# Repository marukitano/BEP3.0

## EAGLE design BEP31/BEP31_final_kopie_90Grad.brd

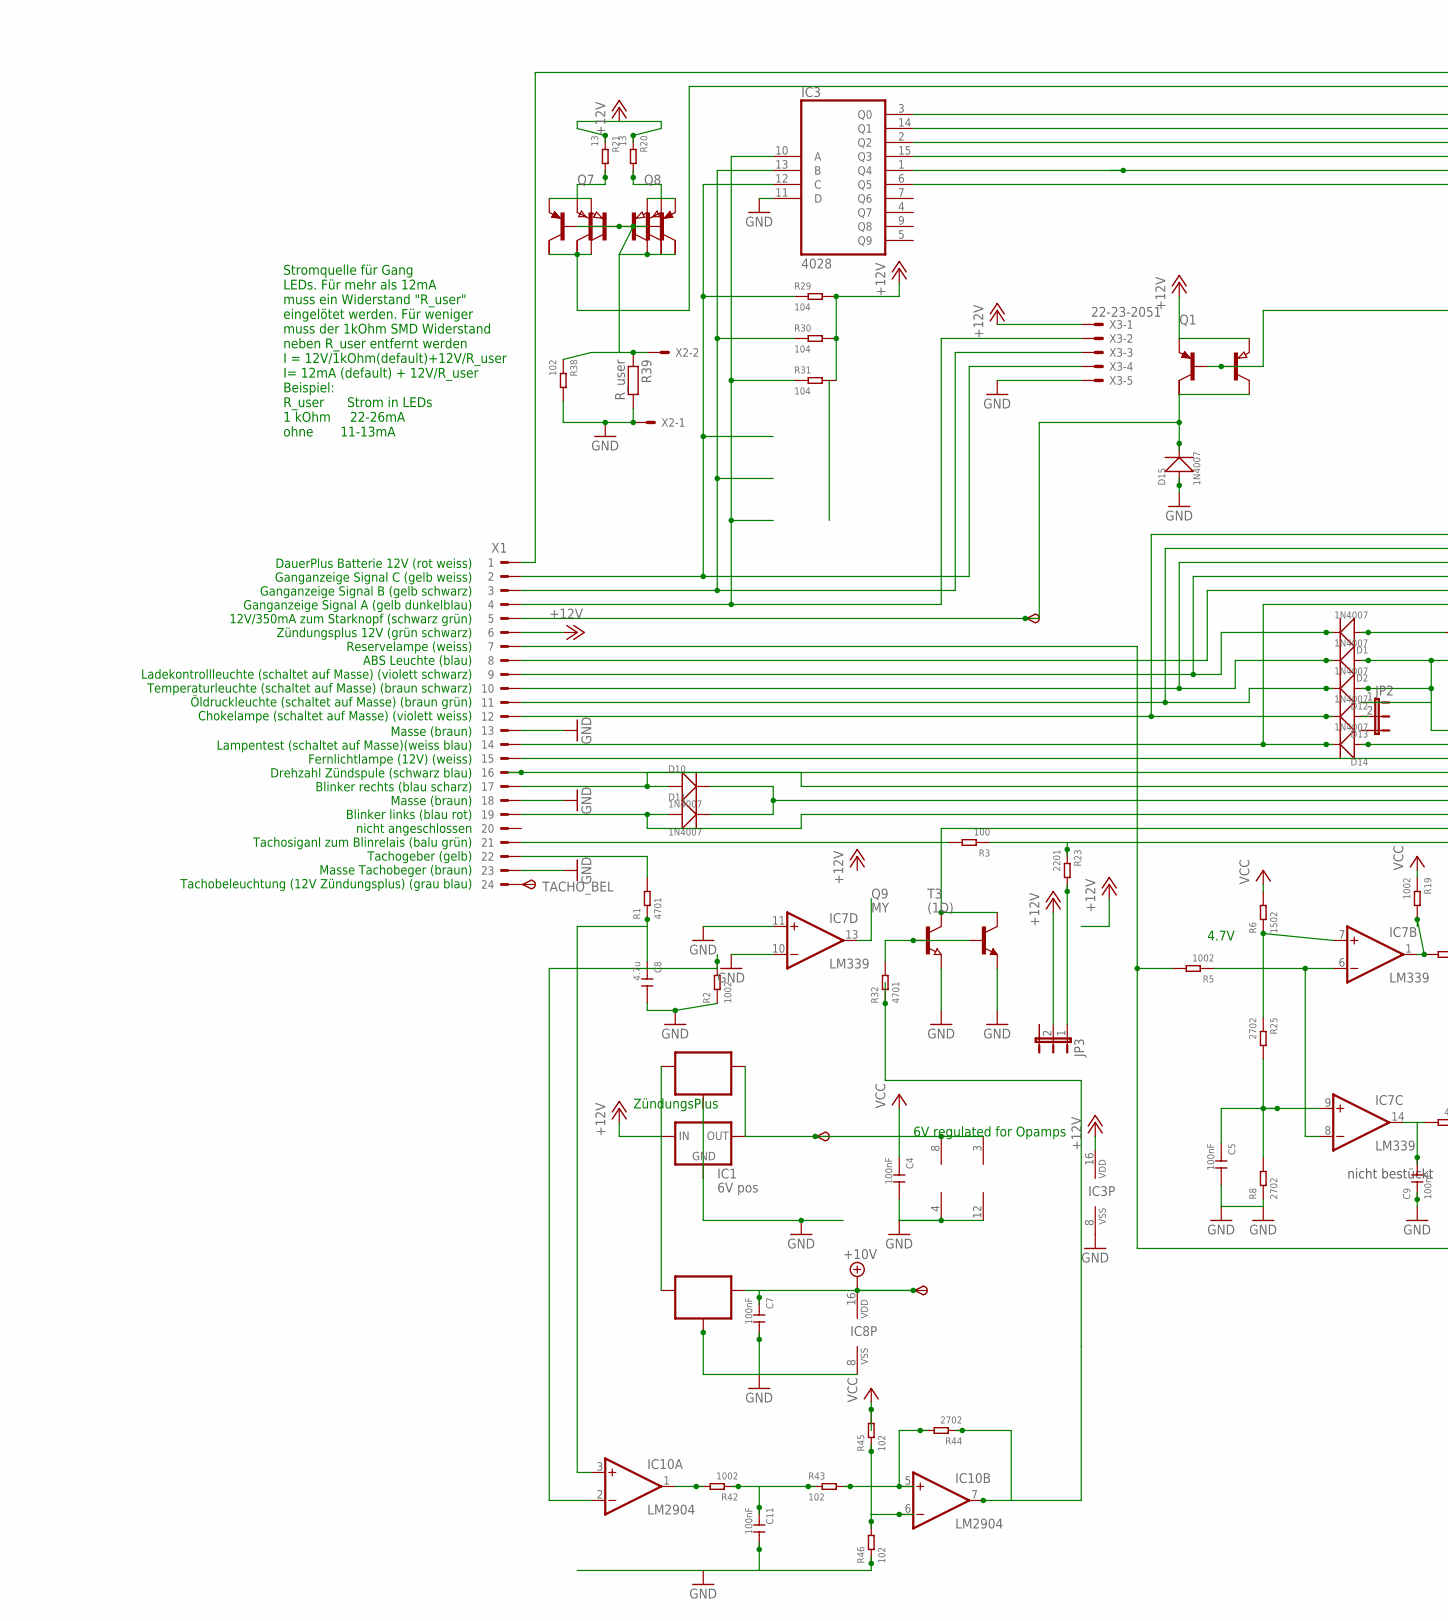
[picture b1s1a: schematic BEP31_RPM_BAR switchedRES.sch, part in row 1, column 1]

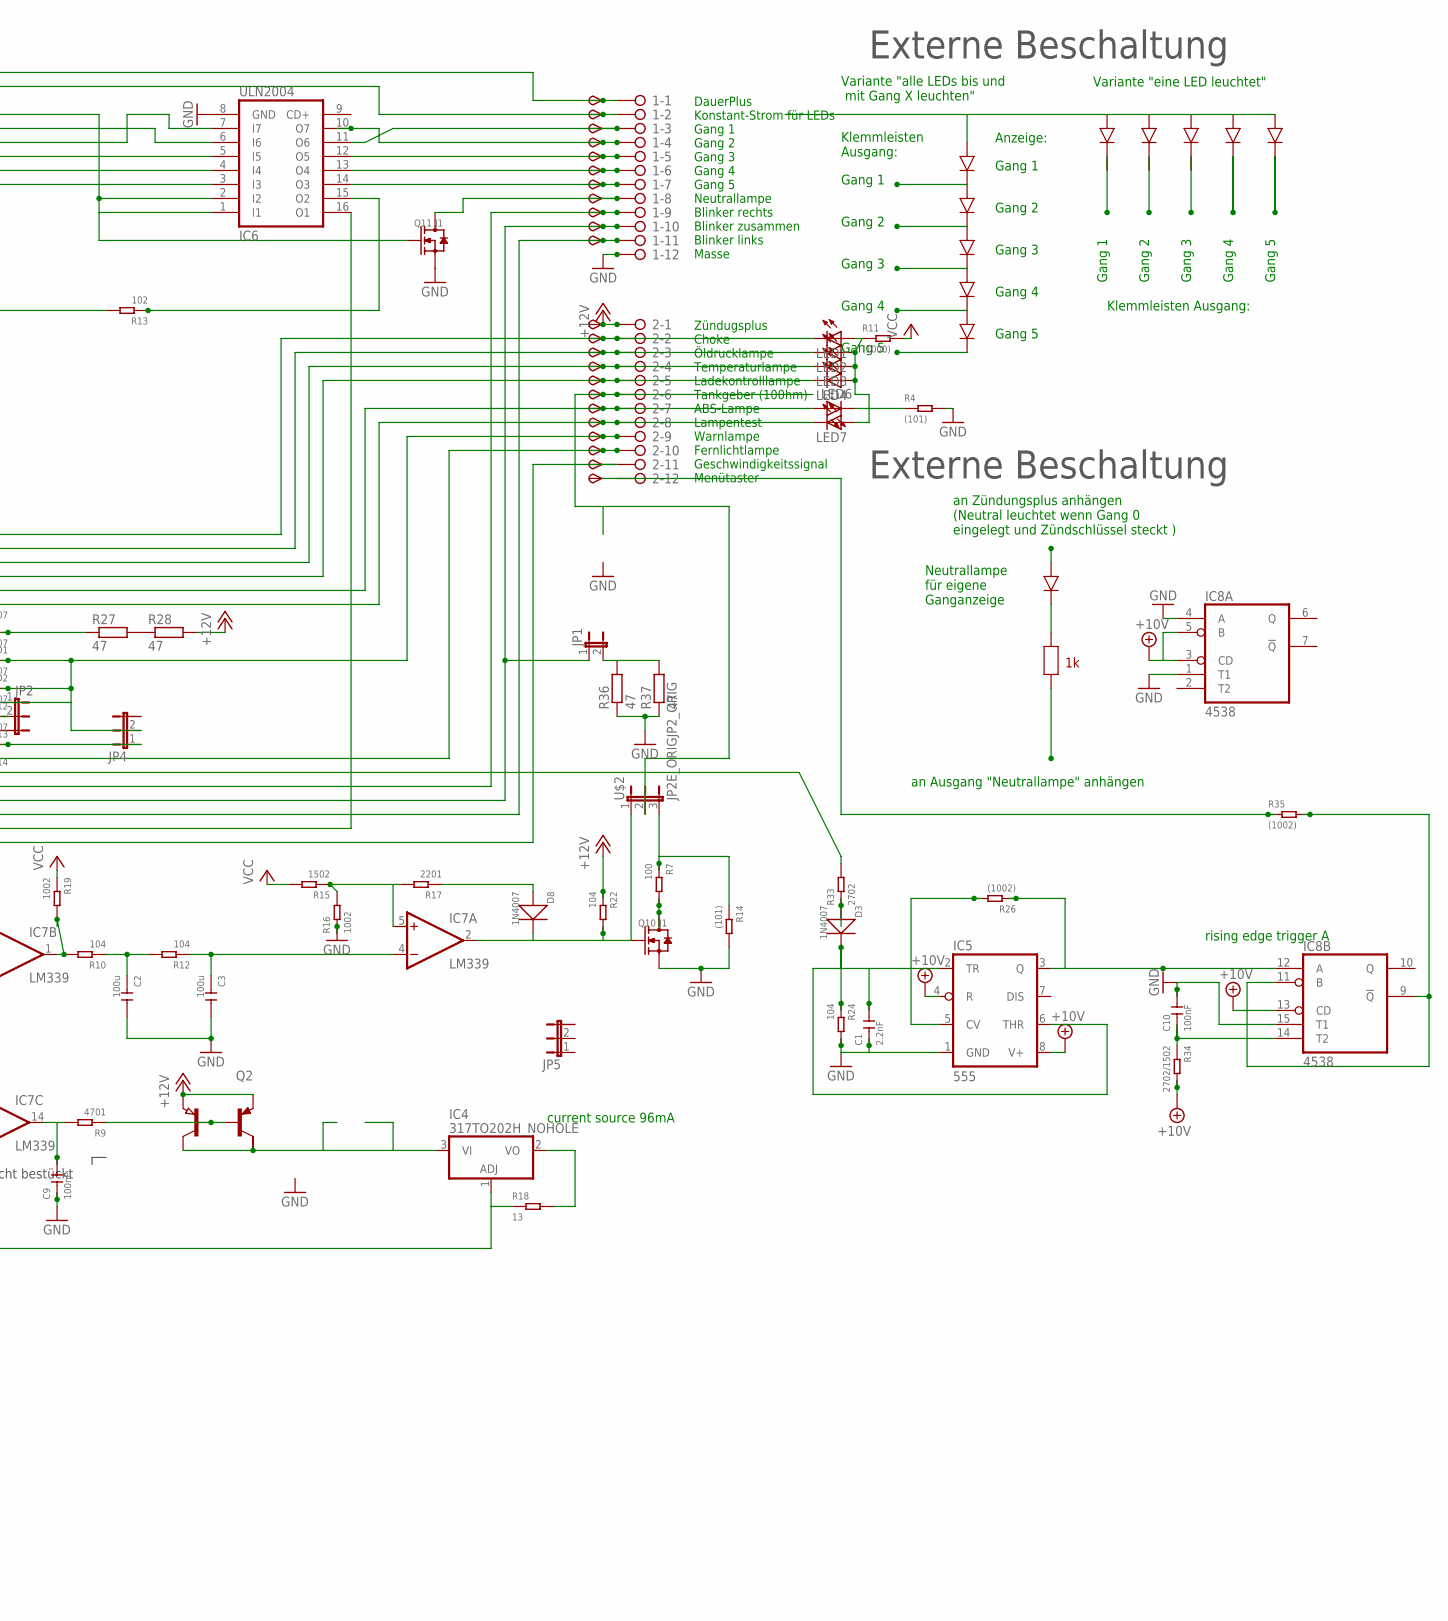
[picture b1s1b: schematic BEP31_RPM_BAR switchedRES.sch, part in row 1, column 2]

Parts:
1, 2: 2081-1132; 12-PIN
6V, 10V: TPSB1.8; B1.8
C1: 2.2nF; C0805
C2, C3: 100u; C1206
C4, C5, C7, C9, C10, C11: 100nF; C0805
C8: 4.7u; C0805
D1, D3, D8, D10, D11, D15: 1N4007; DO-214AC
D2, D12, D13, D14: 1N4007; DO-214AC-1206MOUNT
IC1: 6V pos; 78LXX
IC2, IC9: 78LXXSOT89_ROUND; SOT89_ROUND
IC3: 4028; SO16
IC4: 317TO202H_NOHOLE; TO220H_NOHOLE
IC5: 555; SO08
IC6: ULN2004; SO16
IC7: LM339; SO14
IC8: 4538; SO16
IC10: LM2904; SO08
JP1: JP1E; JP1
JP2, JP3, JP4, JP5: JP2E; JP2
LED1, LED2, LED3, LED4, LED6, LED7: LEDLD260; LD260
Q1, Q2, Q7, Q8: PNP-TRANSISTOR_SOT89; SOT89
Q3: AH-16; SOT223
Q4, Q5, Q6: (AH-16); SOT223
Q9: MY; SOT89
Q10, Q11: J1; SOT-23
R1, R9, R32: 4701; R0805
R2, R5, R16, R19, R42: 1002; R0805
R3, R7: 100; R0805
R4, R14: (101); R0805
R6, R15: 1502; R0805
R8, R25, R33, R44: 2702; R0805
R10, R12, R22, R24, R29, R30, R31: 104; R0805
R11: (1000); R0805
R13, R38, R43, R45, R46: 102; R0805
R17, R23: 2201; R0805
R18, R20, R21: 13; R1206
R26, R35: (1002); R0805
R27, R28, R36, R37: 47; V235/17_1MM
R34: 2702/1502; R0805
R39: R_user; R0805
START: TPSB1.8; B1.8
T1: PNP2SM8; SM8
T3: (1D); SOT23-BEC
TACHO_BEL: TPSP1_1MM; P1_1.0MM
TP1, TP2, TP3, TP4, TP5, TP6, TP7, TP8, TP9, TP10, TP11, TP12, TP16, TP17, TP18, TP19, TP21, TP22, TP23, TP25, TP26: TPSB1.8; B1.8
TP13, TP24: TPSB1,27; B1,27
U$2: JP2E_ORIGJP2_ORIG; JP2_ORIG
X1: CON_BMWV2; 24-PIN_V2
X2: 22-23-2021
X3: 22-23-2051

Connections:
+10V: 10V.TP, C7.1, IC5.4 (R), IC5.8 (V+), IC8.3 (CD), IC8.5 (B), IC8.13 (CD), IC8.16 (VDD), IC9.1 (OUT), R34.2
+12V: 2.1, IC1.IN, IC2.3 (IN), IC3.16 (VDD), IC9.3 (IN), JP3.2, Q1.3 (E), Q2.3 (E), Q3.3 (E), Q4.3 (E), R20.1, R21.1, R22.1, R28.2, R29.2, R30.2, R31.2, TP12.TP, X1.6, X3.1; also elsewhere on the board
+12V1: IC10.7 (OUT), R32.1, R44.1
GND: 1.12, C1.1, C2.2, C3.2, C4.2, C5.2, C7.2, C8.2, C9.1, C10.2, C11.2, D15.1 (+), IC1.GND, IC2.2 (GND), IC2.2@1 (GND), IC3.8 (VSS), IC3.11 (D), IC5.1 (GND), IC6.8 (GND), IC7.10 (-IN), IC7.11 (+IN), IC7.12 (GND), IC8.1 (T1), IC8.4 (A), IC8.8 (VSS), IC8.15 (T1), IC9.2 (GND), IC9.2@1 (GND), IC10.4 (V-), Q9.3 (E), Q10.2 (S), Q11.2 (S), R2.1, R4.2, R8.1, R14.2, R16.1, R24.2, R36.1, R37.1, R38.2, R39.2, R46.1, T3.E, X1.13, X1.18, X1.23, X2.1, X3.5; also elsewhere on the board
unnamed: 2.9, D2.1 (+), D12.1 (+), JP2.1, JP4.2, TP24.TP
unnamed 5: IC3.10 (A), R31.1, X1.4, X3.2; also elsewhere on the board
unnamed 6: IC3.13 (B), R30.1, X1.3, X3.3; also elsewhere on the board
unnamed: 2.7, LED6.A, TP22.TP, X1.8
unnamed: Q5.3 (E), Q8.3 (E), R21.2, T1.1 (E)
unnamed: D8.2 (-), IC7.2 (OUT), Q10.1 (G), R22.2, U$2.1
unnamed: IC10.2 (-IN), R2.2
unnamed: R27.2, R28.1
unnamed: Q6.3 (E), Q7.3 (E), R20.2, T1.3 (E)
unnamed: D15.2 (-), Q1.2 (C), Q3.2 (C), START.TP, X1.5
unnamed: 2.2, D13.2 (-), LED1.K (C), TP16.TP, X1.12
unnamed: 2.3, D12.2 (-), LED2.K (C), TP17.TP, X1.11
unnamed: 2.4, D2.2 (-), LED3.K (C), TP18.TP, X1.10
unnamed: IC4.3 (VI), Q2.2 (C), Q4.2 (C)
unnamed: IC7.6 (-IN), IC7.8 (-IN), R5.1
unnamed 20: IC3.12 (C), R29.1, X1.2, X3.4; also elsewhere on the board
unnamed: IC3.15 (Q3), IC6.5 (I5)
unnamed: 2.8, D14.2 (-), LED7.K (C), TP23.TP, X1.14
unnamed: 1.9, D10.1 (+), TP9.TP, X1.17
unnamed: 1.11, D11.1 (+), TP11.TP, X1.19
unnamed: IC8.9 (!Q), IC8.11 (B), R35.2
unnamed 26: R1.2, X1.22; also elsewhere on the board
unnamed: C8.1, IC10.3 (+IN), R1.1
unnamed: 1.6, IC6.13 (O4), TP6.TP
unnamed: 1.7, IC6.14 (O3), TP7.TP
unnamed: 2.11, R3.1, R23.1, TP26.TP
unnamed: 2.6, TP21.TP, U$2.2
unnamed: JP3.1, R23.2
unnamed: C5.1, IC7.9 (+IN), R8.2, R25.2
unnamed: C9.2, IC7.14 (OUT), R9.2
unnamed 35: C1.2, D3.2 (-), IC5.2 (TR), IC5.6 (THR), R24.1; also elsewhere on the board
unnamed: LED6.K (C), R4.1
unnamed: IC4.1 (ADJ), R5.2, R18.1, X1.7
unnamed: Q2.1 (B), Q4.1 (B), R9.1
unnamed: IC3.2 (Q2), IC6.7 (I7)
unnamed: 1.3, IC6.11 (O6), TP3.TP
unnamed: 1.5, IC6.12 (O5), TP5.TP
unnamed: LED1.A, LED2.A, LED3.A, LED4.A, LED7.A, R11.1
unnamed: R33.2, X1.16
unnamed: Q1.1 (B), Q3.1 (B), R13.2
unnamed: IC3.3 (Q0), IC6.1 (I1), IC6.2 (I2), Q11.1 (G)
unnamed: C2.1, R10.1, R12.2
unnamed: C3.1, IC7.4 (-IN), R12.1
unnamed: IC7.5 (+IN), R15.1, R16.2, R17.2
unnamed: Q10.3 (D), R7.2
unnamed: D8.1 (+), R17.1
unnamed: IC3.1 (Q4), IC6.4 (I4)
unnamed: 1.8, Q11.3 (D), TP8.TP
unnamed: 2.10, TP25.TP, X1.15
unnamed: D1.1 (+), R27.1
unnamed: 2.5, D1.2 (-), LED4.K (C), TP19.TP, X1.9
unnamed: IC3.14 (Q1), IC6.6 (I6)
unnamed: Q5.1 (B), Q6.1 (B), Q6.2 (C), Q7.1 (B), Q7.2 (C), Q8.1 (B), R38.1, R39.1, T1.2 (B), T1.4 (B), T1.6 (C1), X2.2
unnamed: 1.2, Q5.2 (C), Q8.2 (C), T1.8 (C1), TP2.TP
unnamed: IC3.6 (Q5), IC6.3 (I3)
unnamed: IC4.2 (VO), R18.2
unnamed: IC5.5 (CV), R26.2
unnamed: 1.4, IC6.10 (O7), TP4.TP
unnamed: 1.1, TP1.TP, X1.1
unnamed: IC7.7 (+IN), R6.1, R25.1
unnamed: IC6.16 (O1), Q9.2 (C), R3.2, T3.C, X1.21
unnamed: Q9.1 (B), R32.2, T3.B
unnamed: IC5.3 (Q), IC8.12 (A), R26.1
unnamed: D3.1 (+), R33.1
unnamed: IC6.15 (O2), R13.1
unnamed: C10.1, IC8.14 (T2), R34.1
unnamed: 2.12, R35.1, TP13.TP
unnamed: IC10.1 (OUT), R42.2
unnamed 83: 1.10, D10.2 (-), D11.2 (-), JP1.1, TP10.TP; also elsewhere on the board
unnamed 84: JP1.2, R36.2, R37.2; also elsewhere on the board
unnamed: D13.1 (+), JP2.2
unnamed: C11.1, R42.1, R43.1
unnamed: IC10.5 (+IN), R43.2, R44.2
unnamed: D14.1 (+), JP4.1
unnamed: R7.1, R14.1, U$2.3
unnamed: IC10.6 (-IN), R45.1, R46.2
unnamed: IC7.1 (OUT), R10.2, R19.2
unnamed: TACHO_BEL.TP, X1.24
VCC: 6V.TP, C4.1, IC1.OUT, IC2.1 (OUT), IC7.3 (V+), IC10.8 (V+), R6.2, R11.2, R15.2, R19.1, R45.2

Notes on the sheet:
6V regulated for Opamps
current source 96mA
ZündungsPlus
Zündugsplus Choke Öldrucklampe Temperaturlampe Ladekontrolllampe Tankgeber (100hm) ABS-Lampe Lampentest Warnlampe Fernlichtlampe Geschwindigkeitssignal Menütaster
DauerPlus Konstant-Strom für LEDs Gang 1 Gang 2 Gang 3 Gang 4 Gang 5 Neutrallampe Blinker rechts Blinker zusammen Blinker links Masse
DauerPlus Batterie 12V (rot weiss) Ganganzeige Signal C (gelb weiss) Ganganzeige Signal B (gelb schwarz) Ganganzeige Signal A (gelb dunkelblau) 12V/350mA zum Starknopf (schwarz grün) Zündungsplus 12V (grün schwarz) Reservelampe (weiss) ABS Leuchte (blau) Ladekontrollleuchte (schaltet auf Masse) (vi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
Masse (braun) Lampentest (schaltet auf Masse)(weiss blau) Fernlichtlampe (12V) (weiss) Drehzahl Zündspule (schwarz blau) Blinker rechts (blau scharz) Masse (braun) Blinker links (blau rot) nicht angeschlossen Tachosiganl zum Blinrelais (balu grün) Tachogeber (gelb) Masse Tachobeger (braun) Tachobel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
4.7V
Stromquelle für Gang LEDs. Für mehr als 12mA muss ein Widerstand "R_user" eingelötet werden. Für weniger muss der 1kOhm SMD Widerstand neben R_user entfernt werden I = 12V/1kOhm(default)+12V/R_user I= 12mA (default) + 12V/R_user Beispiel: R_user Strom in LEDs 1 kOhm 22-26mA ohne 11-13mA
Gang 1
Gang 2
Gang 3
Gang 4
Gang 5
Variante "eine LED leuchtet"
Variante "alle LEDs bis und mit Gang X leuchten"
Klemmleisten Ausgang:
Klemmleisten Ausgang:
an Zündungsplus anhängen (Neutral leuchtet wenn Gang 0 eingelegt und Zündschlüssel steckt )
an Ausgang "Neutrallampe" anhängen
Neutrallampe für eigene Ganganzeige
Externe Beschaltung
Anzeige:
nicht bestückt
rising edge trigger A

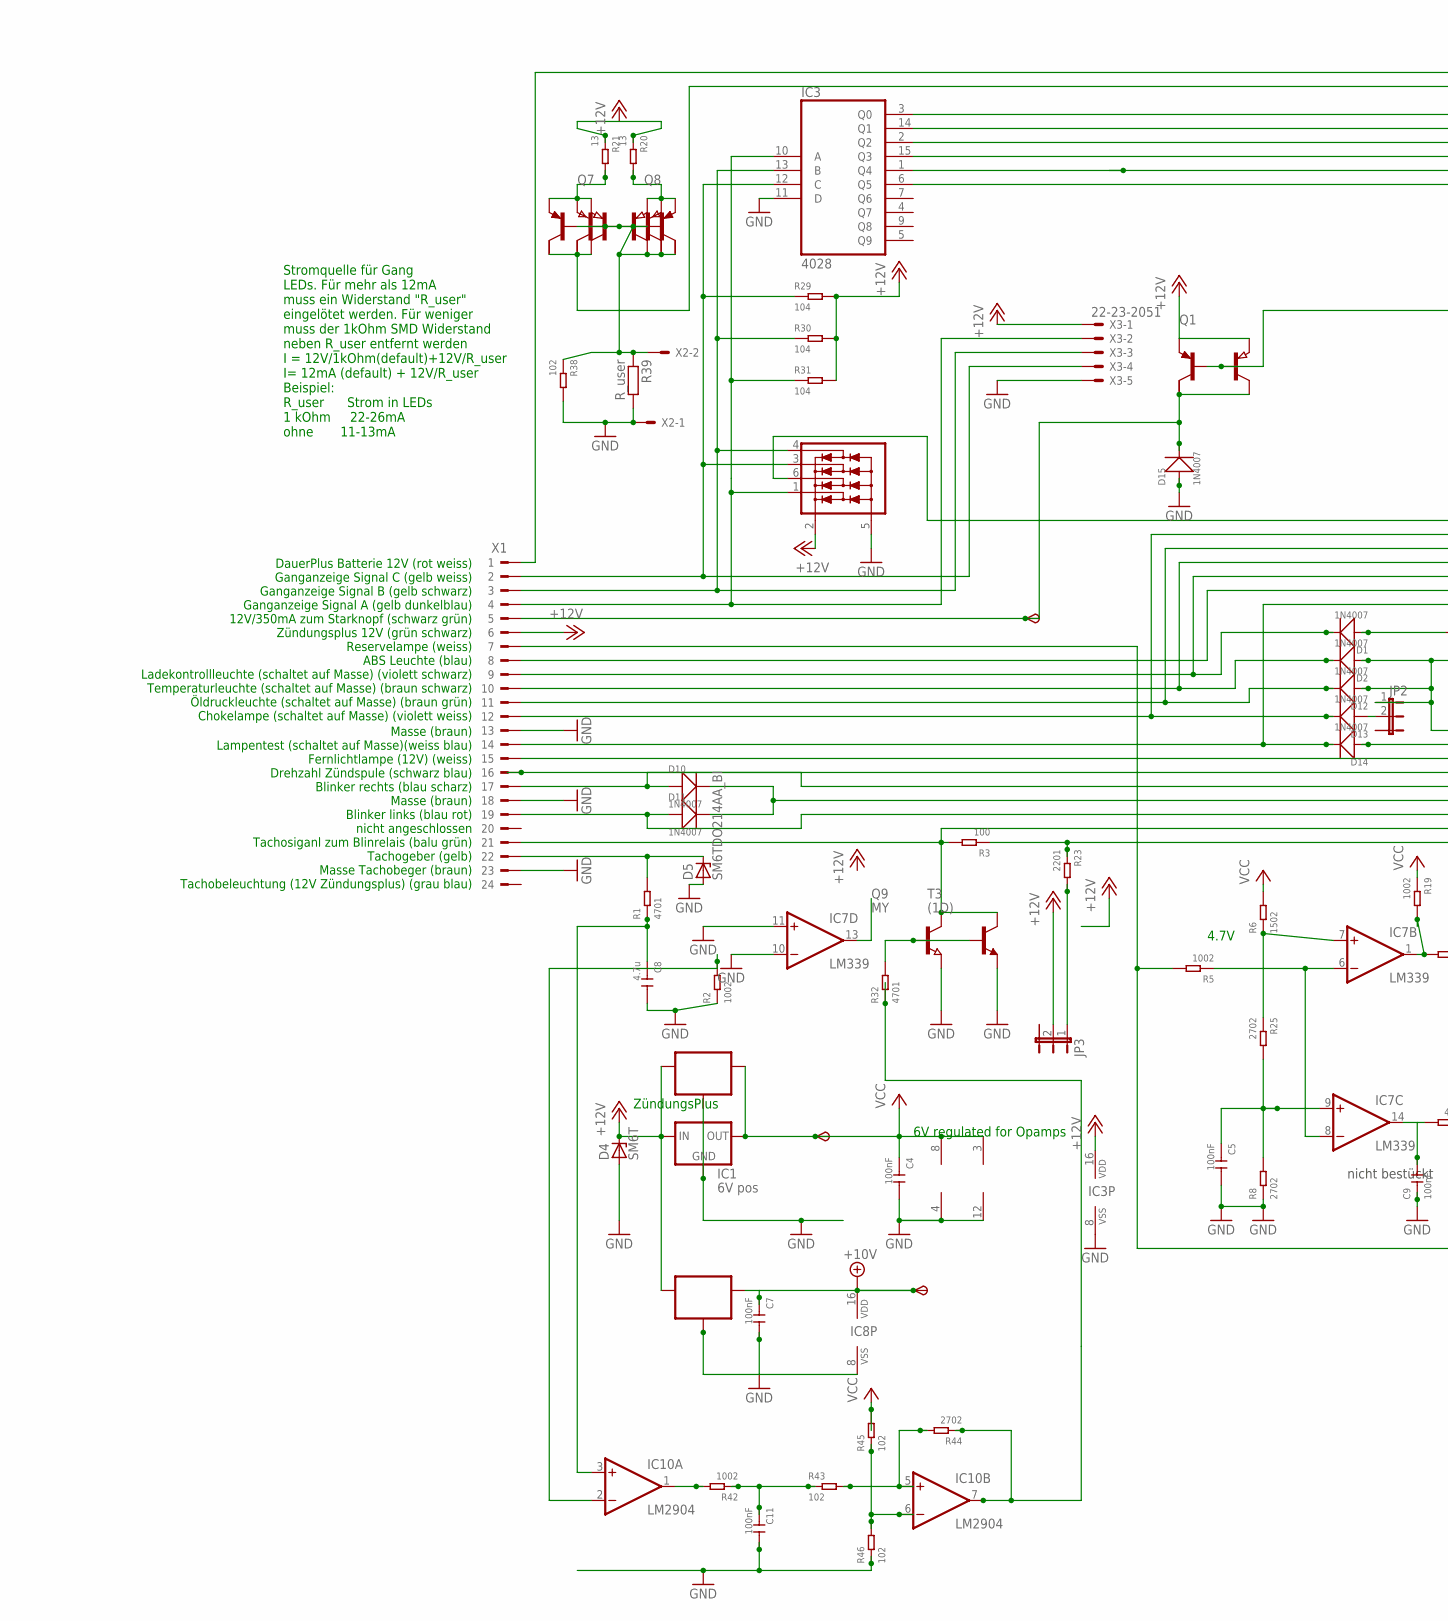
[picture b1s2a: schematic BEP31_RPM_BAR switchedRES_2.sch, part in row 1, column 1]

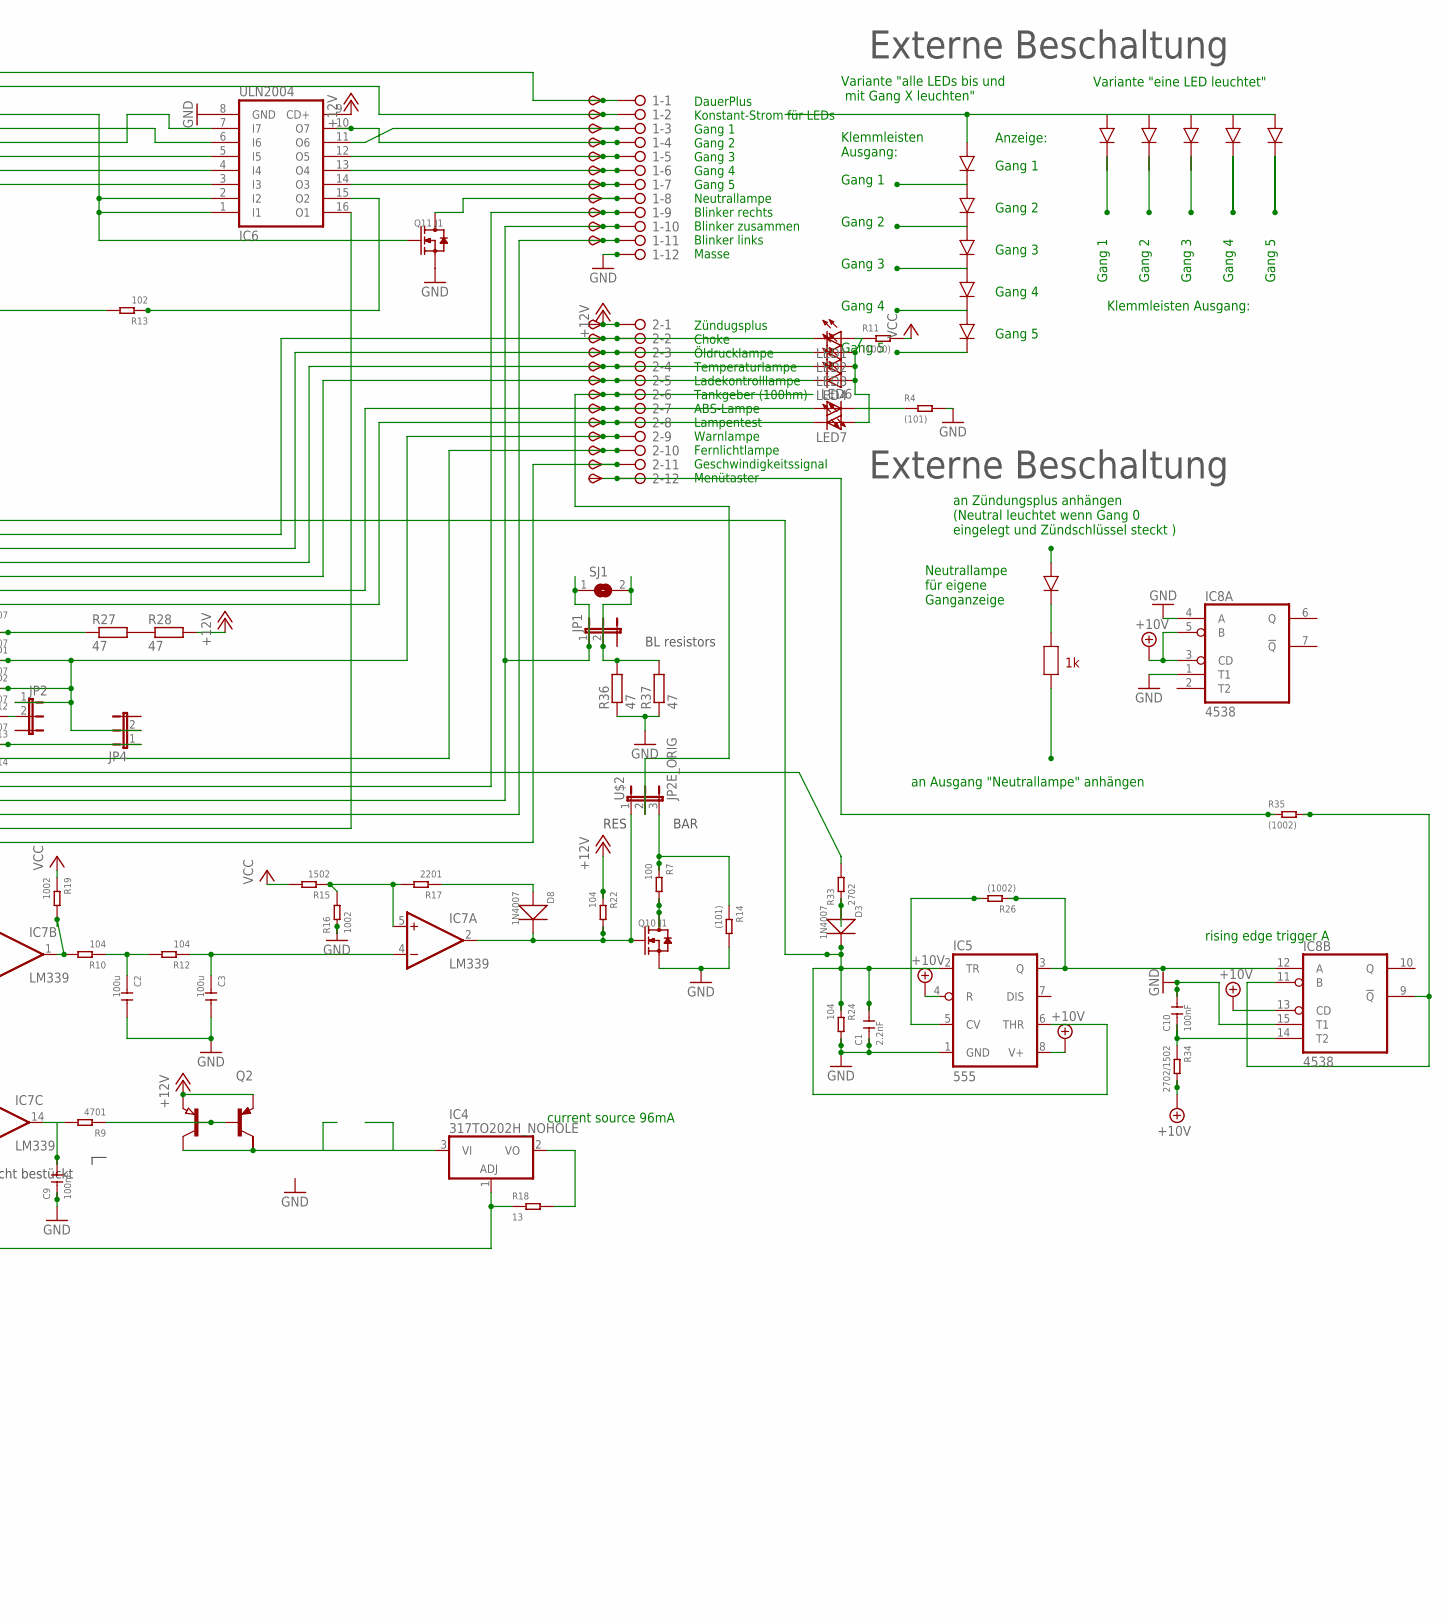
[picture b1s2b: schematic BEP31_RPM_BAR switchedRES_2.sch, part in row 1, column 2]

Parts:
1, 2: 2081-1132; 12-PIN
6V, 10V: TPSB2.0; B2.0
C1: 2.2nF; C0805
C2, C3: 100u; C1206
C4, C5, C7, C9, C10, C11: 100nF; C0805
C8: 4.7u; C0805
D1, D3, D8, D10, D11, D15: 1N4007; DO-214AC
D2, D12, D13, D14: 1N4007; DO-214AC-1206MOUNT
D4: SM6T; DO214AA
D5: SM6TDO214AA_BI; DO214AA_BI
IC1: 6V pos; 78LXX
IC2, IC9: 78LXXSOT89_ROUND; SOT89_ROUND
IC3: 4028; SO16
IC4: 317TO202H_NOHOLE; TO220H_NOHOLE
IC5: 555; SO08
IC6: ULN2004; SO16
IC7: LM339; SO14
IC8: 4538; SO16
IC10: LM2904; SO08
JP1, JP2, JP3, JP4: JP2EJP2_SMALLPADS; JP2_SMALLPADS
LED1, LED2, LED3, LED4, LED6, LED7: LEDLD260; LD260
Q1, Q2, Q7, Q8: PNP-TRANSISTOR_SOT89; SOT89
Q3: AH-16; SOT223
Q4, Q5, Q6: (AH-16); SOT223
Q9: MY; SOT89
Q10, Q11: J1; SOT-23
R1, R9, R32: 4701; R0805
R2, R5, R16, R19, R42: 1002; R0805
R3, R7: 100; R0805
R4, R14: (101); R0805
R6, R15: 1502; R0805
R8, R25, R33, R44: 2702; R0805
R10, R12, R22, R24, R29, R30, R31: 104; R0805
R11: (1000); R0805
R13, R38, R43, R45, R46: 102; R0805
R17, R23: 2201; R0805
R18, R20, R21: 13; R1206
R26, R35: (1002); R0805
R27, R28, R36, R37: 47; V235/17_1MM
R34: 2702/1502; R0805
R39: R_user; R0805
SJ1: SJ
START: TPSB2.0; B2.0
T1: PNP2SM8; SM8
T3: (1D); SOT23-BEC
TP1, TP2, TP3, TP4, TP5, TP6, TP7, TP8, TP9, TP10, TP11, TP12, TP13, TP16, TP17, TP18, TP19, TP21, TP22, TP23, TP25, TP26: TPSB2.0; B2.0
TP24: TPSB1,27; B1,27
U$2: JP2E_ORIG; JP2_ORIG_SMALLPADS
U$3: NUP4304SOT457_R; SOT457R_PHILIPS
X1: CON_BMWV2; 24-PIN_V2
X2: 22-23-2021
X3: 22-23-2051

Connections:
+10V: 10V.TP, C7.1, IC5.4 (R), IC5.8 (V+), IC8.3 (CD), IC8.5 (B), IC8.13 (CD), IC8.16 (VDD), IC9.1 (OUT), R34.2
+12V: 2.1, D4.C, IC1.IN, IC2.3 (IN), IC3.16 (VDD), IC6.9 (CD+), IC9.3 (IN), JP3.2, Q1.3 (E), Q2.3 (E), Q3.3 (E), Q4.3 (E), R20.1, R21.1, R22.1, R28.2, R29.2, R30.2, R31.2, TP12.TP, U$3.2 (V+), X1.6, X3.1
+12V1: IC10.7 (OUT), R32.1, R44.1
GND: 1.12, C1.1, C2.2, C3.2, C4.2, C5.2, C7.2, C8.2, C9.1, C10.2, C11.2, D4.A, D5.A, D15.1 (+), IC1.GND, IC2.2 (GND), IC2.2@1 (GND), IC3.8 (VSS), IC3.11 (D), IC5.1 (GND), IC6.8 (GND), IC7.10 (-IN), IC7.11 (+IN), IC7.12 (GND), IC8.1 (T1), IC8.4 (A), IC8.8 (VSS), IC8.15 (T1), IC9.2 (GND), IC9.2@1 (GND), IC10.4 (V-), Q9.3 (E), Q10.2 (S), Q11.2 (S), R2.1, R4.2, R8.1, R14.2, R16.1, R24.2, R36.1, R37.1, R38.2, R39.2, R46.1, T3.E, U$3.5 (V-), X1.13, X1.18, X1.23, X2.1, X3.5
unnamed: 2.9, D2.1 (+), D12.1 (+), JP2.1, JP4.2, TP24.TP
unnamed: IC3.10 (A), R31.1, U$3.1 (D1), X1.4, X3.2
unnamed: IC3.13 (B), R30.1, U$3.4 (D4), X1.3, X3.3
unnamed: 2.7, LED6.A, TP22.TP, X1.8
unnamed: Q5.3 (E), Q8.3 (E), R21.2, T1.1 (E)
unnamed: D8.2 (-), IC7.2 (OUT), Q10.1 (G), R22.2, U$2.1
unnamed: IC10.2 (-IN), R2.2
unnamed: R27.2, R28.1
unnamed: Q6.3 (E), Q7.3 (E), R20.2, T1.3 (E)
unnamed: D15.2 (-), Q1.2 (C), Q3.2 (C), START.TP, X1.5
unnamed: 2.2, D13.2 (-), LED1.K (C), TP16.TP, X1.12
unnamed: 2.3, D12.2 (-), LED2.K (C), TP17.TP, X1.11
unnamed: 2.4, D2.2 (-), LED3.K (C), TP18.TP, X1.10
unnamed: IC4.3 (VI), Q2.2 (C), Q4.2 (C)
unnamed: IC7.6 (-IN), IC7.8 (-IN), R5.1
unnamed: IC3.12 (C), R29.1, U$3.3 (D3), X1.2, X3.4
unnamed: IC3.15 (Q3), IC6.5 (I5)
unnamed: 2.8, D14.2 (-), LED7.K (C), TP23.TP, X1.14
unnamed: 1.9, D10.1 (+), TP9.TP, X1.17
unnamed: 1.11, D11.1 (+), TP11.TP, X1.19
unnamed: IC8.9 (!Q), IC8.11 (B), R35.2
unnamed: D5.C, R1.2, X1.22
unnamed: C8.1, IC10.3 (+IN), R1.1
unnamed: 1.6, IC6.13 (O4), TP6.TP
unnamed: 1.7, IC6.14 (O3), TP7.TP
unnamed: 2.11, R3.1, R23.1, TP26.TP
unnamed: 2.6, TP21.TP, U$2.2
unnamed: JP3.1, R23.2
unnamed: C5.1, IC7.9 (+IN), R8.2, R25.2
unnamed: C9.2, IC7.14 (OUT), R9.2
unnamed: C1.2, D3.2 (-), IC5.2 (TR), IC5.6 (THR), R24.1, U$3.6 (D2)
unnamed: LED6.K (C), R4.1
unnamed: IC4.1 (ADJ), R5.2, R18.1, X1.7
unnamed: Q2.1 (B), Q4.1 (B), R9.1
unnamed: IC3.2 (Q2), IC6.7 (I7)
unnamed: 1.3, IC6.11 (O6), TP3.TP
unnamed: 1.5, IC6.12 (O5), TP5.TP
unnamed: LED1.A, LED2.A, LED3.A, LED4.A, LED7.A, R11.1
unnamed: R33.2, X1.16
unnamed: Q1.1 (B), Q3.1 (B), R13.2
unnamed: IC3.3 (Q0), IC6.1 (I1), IC6.2 (I2), Q11.1 (G)
unnamed: C2.1, R10.1, R12.2
unnamed: C3.1, IC7.4 (-IN), R12.1
unnamed: IC7.5 (+IN), R15.1, R16.2, R17.2
unnamed: Q10.3 (D), R7.2
unnamed: D8.1 (+), R17.1
unnamed: IC3.1 (Q4), IC6.4 (I4)
unnamed: 1.8, Q11.3 (D), TP8.TP
unnamed: 2.10, TP25.TP, X1.15
unnamed: D1.1 (+), R27.1
unnamed: 2.5, D1.2 (-), LED4.K (C), TP19.TP, X1.9
unnamed: IC3.14 (Q1), IC6.6 (I6)
unnamed: Q5.1 (B), Q6.1 (B), Q6.2 (C), Q7.1 (B), Q7.2 (C), Q8.1 (B), R38.1, R39.1, T1.2 (B), T1.4 (B), T1.6 (C1), X2.2
unnamed: 1.2, Q5.2 (C), Q8.2 (C), T1.8 (C1), TP2.TP
unnamed: IC3.6 (Q5), IC6.3 (I3)
unnamed: IC4.2 (VO), R18.2
unnamed: IC5.5 (CV), R26.2
unnamed: 1.4, IC6.10 (O7), TP4.TP
unnamed: 1.1, TP1.TP, X1.1
unnamed: IC7.7 (+IN), R6.1, R25.1
unnamed: IC6.16 (O1), Q9.2 (C), R3.2, T3.C, X1.21
unnamed: Q9.1 (B), R32.2, T3.B
unnamed: IC5.3 (Q), IC8.12 (A), R26.1
unnamed: D3.1 (+), R33.1
unnamed: IC6.15 (O2), R13.1
unnamed: C10.1, IC8.14 (T2), R34.1
unnamed: 2.12, R35.1, TP13.TP
unnamed: IC10.1 (OUT), R42.2
unnamed: 1.10, D10.2 (-), D11.2 (-), JP1.1, SJ1.1, TP10.TP
unnamed: JP1.2, R36.2, R37.2, SJ1.2
unnamed: D13.1 (+), JP2.2
unnamed: C11.1, R42.1, R43.1
unnamed: IC10.5 (+IN), R43.2, R44.2
unnamed: D14.1 (+), JP4.1
unnamed: R7.1, R14.1, U$2.3
unnamed: IC10.6 (-IN), R45.1, R46.2
unnamed: IC7.1 (OUT), R10.2, R19.2
VCC: 6V.TP, C4.1, IC1.OUT, IC2.1 (OUT), IC7.3 (V+), IC10.8 (V+), R6.2, R11.2, R15.2, R19.1, R45.2

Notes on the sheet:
6V regulated for Opamps
current source 96mA
ZündungsPlus
Zündugsplus Choke Öldrucklampe Temperaturlampe Ladekontrolllampe Tankgeber (100hm) ABS-Lampe Lampentest Warnlampe Fernlichtlampe Geschwindigkeitssignal Menütaster
DauerPlus Konstant-Strom für LEDs Gang 1 Gang 2 Gang 3 Gang 4 Gang 5 Neutrallampe Blinker rechts Blinker zusammen Blinker links Masse
DauerPlus Batterie 12V (rot weiss) Ganganzeige Signal C (gelb weiss) Ganganzeige Signal B (gelb schwarz) Ganganzeige Signal A (gelb dunkelblau) 12V/350mA zum Starknopf (schwarz grün) Zündungsplus 12V (grün schwarz) Reservelampe (weiss) ABS Leuchte (blau) Ladekontrollleuchte (schaltet auf Masse) (vi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
Masse (braun) Lampentest (schaltet auf Masse)(weiss blau) Fernlichtlampe (12V) (weiss) Drehzahl Zündspule (schwarz blau) Blinker rechts (blau scharz) Masse (braun) Blinker links (blau rot) nicht angeschlossen Tachosiganl zum Blinrelais (balu grün) Tachogeber (gelb) Masse Tachobeger (braun) Tachobel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
4.7V
Stromquelle für Gang LEDs. Für mehr als 12mA muss ein Widerstand "R_user" eingelötet werden. Für weniger muss der 1kOhm SMD Widerstand neben R_user entfernt werden I = 12V/1kOhm(default)+12V/R_user I= 12mA (default) + 12V/R_user Beispiel: R_user Strom in LEDs 1 kOhm 22-26mA ohne 11-13mA
Gang 1
Gang 2
Gang 3
Gang 4
Gang 5
Variante "eine LED leuchtet"
Variante "alle LEDs bis und mit Gang X leuchten"
Klemmleisten Ausgang:
Klemmleisten Ausgang:
an Zündungsplus anhängen (Neutral leuchtet wenn Gang 0 eingelegt und Zündschlüssel steckt )
an Ausgang "Neutrallampe" anhängen
Neutrallampe für eigene Ganganzeige
Externe Beschaltung
Anzeige:
nicht bestückt
rising edge trigger A
BAR
RES
BL resistors
